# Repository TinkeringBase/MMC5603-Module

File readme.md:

[한국어](https://github.com/TinkeringBase/MMC5603-Module/blob/main/readme-ko.md)
# TinkeringBase MMC5603NJ Magnetometer breakout
\
Sensor breakout using MEMSIC's MMC5603NJ Anisotropic Magneto-Resistive (AMR) magnetometer, supports Sparkfun Qwiic system. \
It provides high accuracy of magnetic field data in 3D.

## Specification
±30 G FSR, 20bits operation mode, 0.0625mG per LSB resolution, 2mG total RMS noise, heading accuracy of 1 deg. \
Supply Voltage (VDD): 1.62~3.6V \
Logic Low (VIL): 0.3\*VDD max \
Logic High (VIH): 0.7\*VDD min \
Current consumption: 4mA max \
for more information, see [datasheet](https://www.memsic.com/Public/Uploads/uploadfile/files/20220119/MMC5603NJDatasheetRev.B.pdf)

## I2C address
0x30 only. not changable.

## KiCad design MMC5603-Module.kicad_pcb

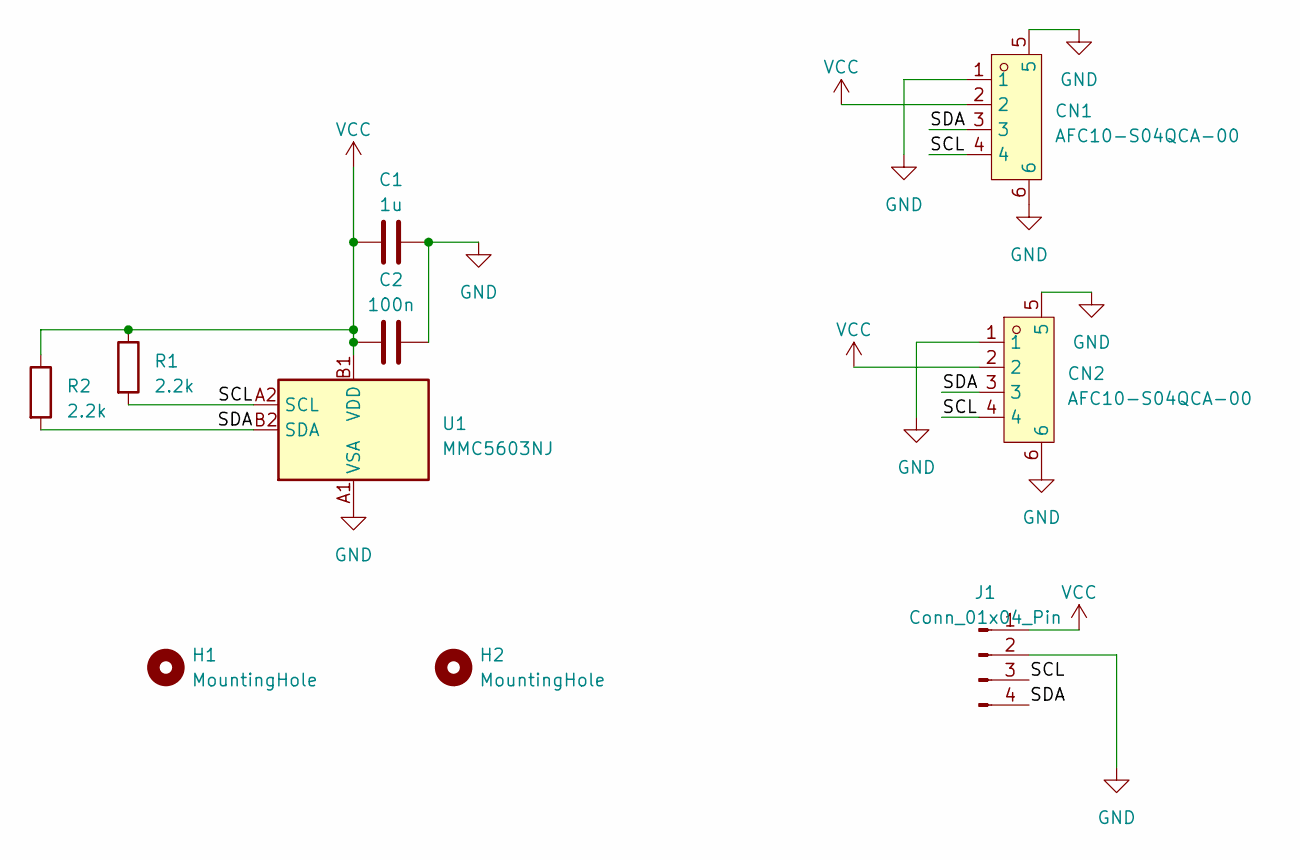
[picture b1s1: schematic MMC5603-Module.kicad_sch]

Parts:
C1: 1u; C_0603_1608Metric
C2: 100n; C_0402_1005Metric
CN1, CN2: AFC10-S04QCA-00; CONN-SMD_AFC10-S04QCA-00; LCSC Part C2764183
H1, H2: MountingHole; MountingHole_2.2mm_M2
J1: Conn_01x04_Pin; PinSocket_1x04_P2.54mm_Vertical
R1, R2: 2.2k; R_0402_1005Metric
U1: MMC5603NJ; WLP-4_0.86x0.86mm_P0.4mm

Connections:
/SCL: CN1.4, CN2.4, J1.3, R1.2, U1.A2 (SCL)
/SDA: CN1.3, CN2.3, J1.4, R2.2, U1.B2 (SDA)
GND: C1.2, C2.2, CN1.1, CN1.5, CN1.6, CN2.1, CN2.5, CN2.6, J1.2, U1.A1 (VSA)
VCC: C1.1, C2.1, CN1.2, CN2.2, J1.1, R1.1, R2.1, U1.B1 (VDD)

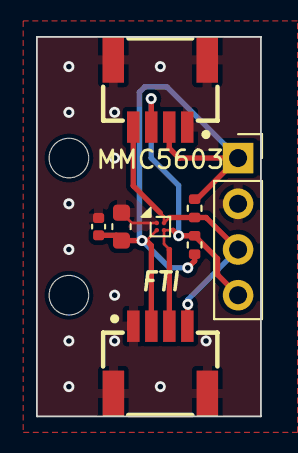
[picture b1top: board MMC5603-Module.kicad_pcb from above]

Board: 2 copper layers, 12.4 x 21.1 mm, 10 parts (0 on the bottom side), 4 nets.

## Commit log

2024-02-19 update license
2024-04-16 ditch logic shift, fix qwiic pinout, documentation
2024-05-10 gitignore
